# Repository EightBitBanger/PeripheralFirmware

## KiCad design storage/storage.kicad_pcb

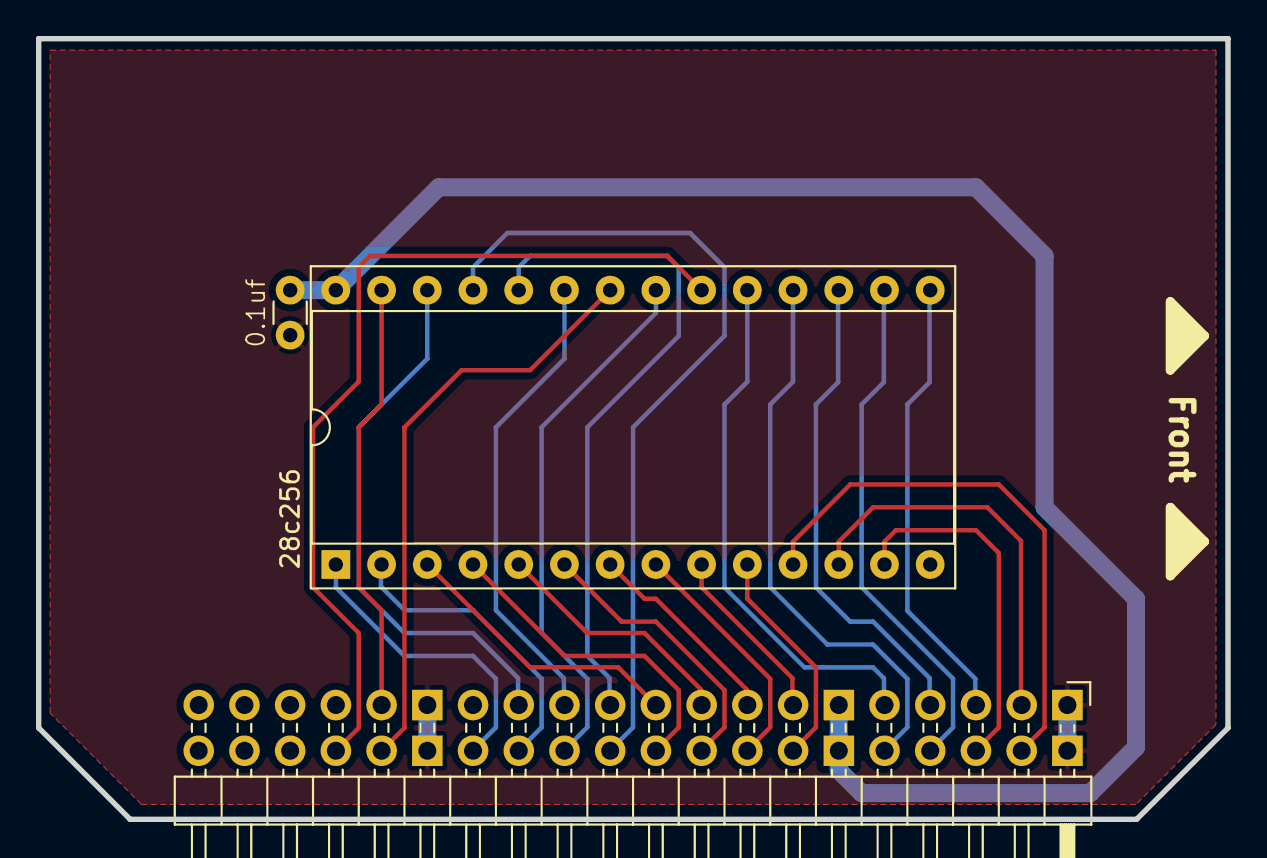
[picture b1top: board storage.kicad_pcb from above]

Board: 2 copper layers, 66.1 x 43.4 mm, 3 parts (0 on the bottom side), 2 nets.

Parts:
0.1uf: C_Disc_D3.0mm_W1.6mm_P2.50mm
20pin conn.: PinHeader_2x20_P2.54mm_Horizontal
28c256: DIP-28_W15.24mm_Socket

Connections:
+5: 0.1uf.1, 20pin conn..11, 20pin conn..12, 28c256.28
GND: 0.1uf.2, 20pin conn..1, 20pin conn..2, 20pin conn..29, 20pin conn..30

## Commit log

2024-08-04 Network peripheral firmware backup
2025-05-27 128x64 display controller
2025-05-27 Network card designs
2025-05-27 GPIO devices
2025-05-27 Storage devices
